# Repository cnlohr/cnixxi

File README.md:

# cnixxi

My experiment with nixie tubes.

It uses a ch32v003 to both control the nixie tube's cathodes, as well as provide the 180V supply for the nixie tube.

Youtube video:

Schematic:

Board:

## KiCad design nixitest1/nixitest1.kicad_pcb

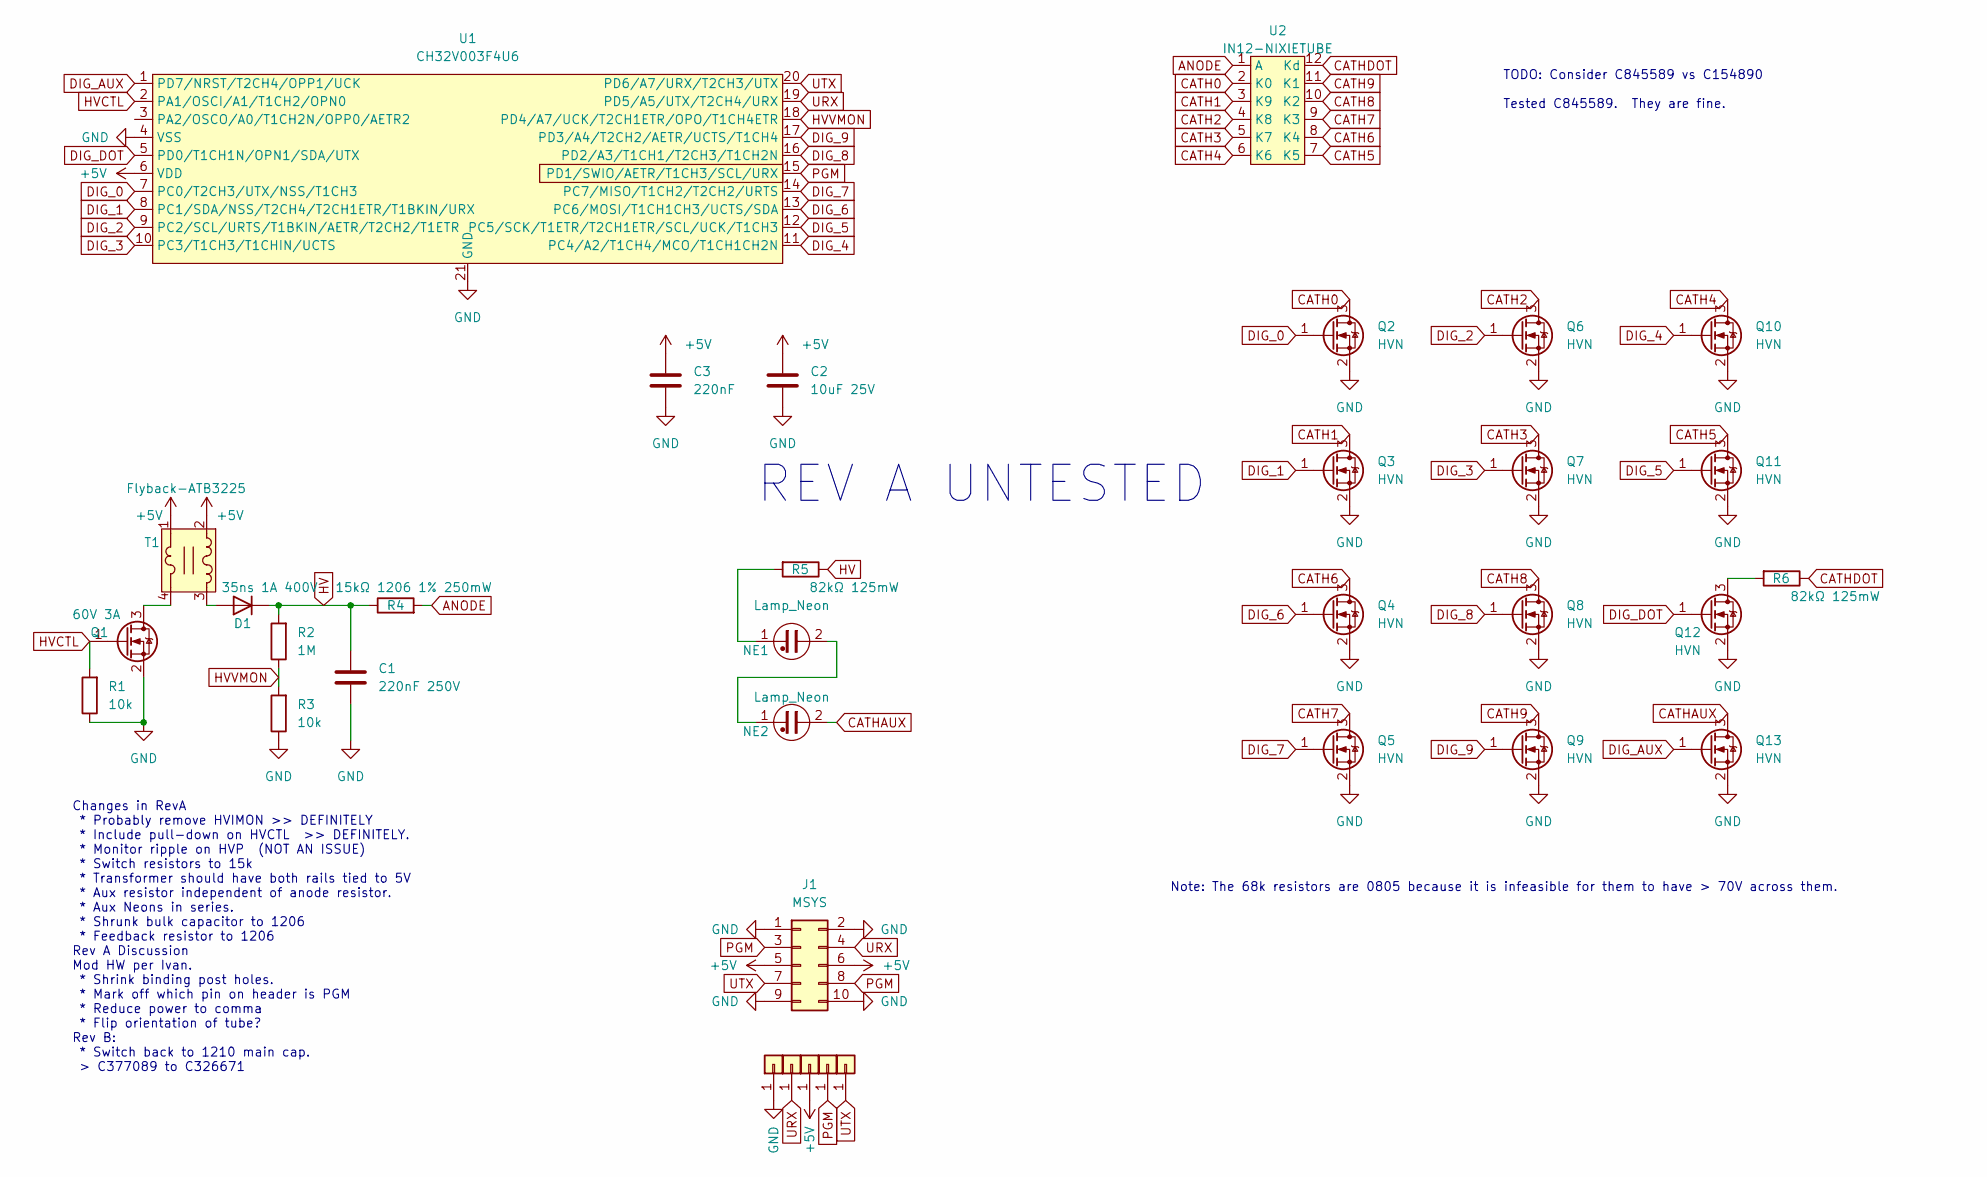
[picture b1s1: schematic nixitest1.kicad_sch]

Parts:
C1: 220nF 250V; C_1210_3225Metric; LCSC C326671
C2: 10uF 25V; C_0603_1608Metric; LCSC C96446
C3: 220nF; C_0402_1005Metric; LCSC C16772
D1: 35ns 1A 400V; D_SOD-123F; LCSC C128697
J1: MSYS; PinHeader_2x05_P2.54mm_Horizontal; LCSC C239336
J2, J3, J4, J5, J6: rawpad22
NE1, NE2: Lamp_Neon; neonglow
Q1: 60V 3A; SOT-23; LCSC C2938374
Q2, Q3, Q4, Q5, Q6, Q7, Q8, Q9, Q10, Q11, Q12, Q13: HVN; SOT-23; LCSC C845589
R1, R3: 10k; R_0402_1005Metric; LCSC C25744
R2: 1M; R_1206_3216Metric; LCSC C108083
R4: 15kΩ 1206 1% 250mW; R_1206_3216Metric; LCSC C114932
R5, R6: 82kΩ 125mW; R_0805_2012Metric; LCSC C136904
T1: Flyback-ATB3225; LCSC C415291
U1: CH32V003F4U6; QFN-20-1EP_3x3mm_P0.4mm_EP1.65x1.65mm; LCSC C5299908
U2: IN12-NIXIETUBE; IN12-NIXIE

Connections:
+5V: C2.1, C3.1, J1.5, J1.6, J3.1, T1.1, T1.2, U1.6 (VDD)
ANODE: R4.2, U2.1 (A)
CATH0: Q2.3 (D), U2.2 (K0)
CATH1: Q3.3 (D), U2.3 (K9)
CATH2: Q6.3 (D), U2.4 (K8)
CATH3: Q7.3 (D), U2.5 (K7)
CATH4: Q10.3 (D), U2.6 (K6)
CATH5: Q11.3 (D), U2.7 (K5)
CATH6: Q4.3 (D), U2.8 (K4)
CATH7: Q5.3 (D), U2.9 (K3)
CATH8: Q8.3 (D), U2.10 (K2)
CATH9: Q9.3 (D), U2.11 (K1)
CATHAUX: NE2.2, Q13.3 (D)
CATHDOT: R6.1, U2.12 (Kd)
DIG_0: Q2.1 (G), U1.7 (PC0/T2CH3/UTX/NSS/T1CH3)
DIG_1: Q3.1 (G), U1.8 (PC1/SDA/NSS/T2CH4/T2CH1ETR/T1BKIN/URX)
DIG_2: Q6.1 (G), U1.9 (PC2/SCL/URTS/T1BKIN/AETR/T2CH2/T1ETR)
DIG_3: Q7.1 (G), U1.10 (PC3/T1CH3/T1CHIN/UCTS)
DIG_4: Q10.1 (G), U1.11 (PC4/A2/T1CH4/MCO/T1CH1CH2N)
DIG_5: Q11.1 (G), U1.12 (PC5/SCK/T1ETR/T2CH1ETR/SCL/UCK/T1CH3)
DIG_6: Q4.1 (G), U1.13 (PC6/MOSI/T1CH1CH3/UCTS/SDA)
DIG_7: Q5.1 (G), U1.14 (PC7/MISO/T1CH2/T2CH2/URTS)
DIG_8: Q8.1 (G), U1.16 (PD2/A3/T1CH1/T2CH3/T1CH2N)
DIG_9: Q9.1 (G), U1.17 (PD3/A4/T2CH2/AETR/UCTS/T1CH4)
DIG_AUX: Q13.1 (G), U1.1 (PD7/NRST/T2CH4/OPP1/UCK)
DIG_DOT: Q12.1 (G), U1.5 (PD0/T1CH1N/OPN1/SDA/UTX)
GND: C1.2, C2.2, C3.2, J1.1, J1.2, J1.9, J1.10, J2.1, Q1.2 (S), Q2.2 (S), Q3.2 (S), Q4.2 (S), Q5.2 (S), Q6.2 (S), Q7.2 (S), Q8.2 (S), Q9.2 (S), Q10.2 (S), Q11.2 (S), Q12.2 (S), Q13.2 (S), R1.1, R3.1, U1.4 (VSS), U1.21 (GND)
HV: C1.1, D1.1 (K), R2.2, R4.1, R5.1
HVCTL: Q1.1 (G), R1.2, U1.2 (PA1/OSCI/A1/T1CH2/OPN0)
HVVMON: R2.1, R3.2, U1.18 (PD4/A7/UCK/T2CH1ETR/OPO/T1CH4ETR)
unnamed: D1.2 (A), T1.3
unnamed: NE1.1, R5.2
unnamed: NE1.2, NE2.1
unnamed: Q1.3 (D), T1.4
unnamed: Q12.3 (D), R6.2
PGM: J1.3, J1.8, J5.1, U1.15 (PD1/SWIO/AETR/T1CH3/SCL/URX)
URX: J1.4, J4.1, U1.19 (PD5/A5/UTX/T2CH4/URX)
UTX: J1.7, J6.1, U1.20 (PD6/A7/URX/T2CH3/UTX)

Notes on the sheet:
TODO: Consider C845589 vs C154890 Tested C845589. They are fine.
Changes in RevA * Probably remove HVIMON >> DEFINITELY * Include pull-down on HVCTL >> DEFINITELY. * Monitor ripple on HVP (NOT AN ISSUE) * Switch resistors to 15k * Transformer should have both rails tied to 5V * Aux resistor independent of anode resistor. * Aux Neons in series. * Shrunk bulk capa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
REV A UNTESTED
Note: The 68k resistors are 0805 because it is infeasible for them to have > 70V across them.

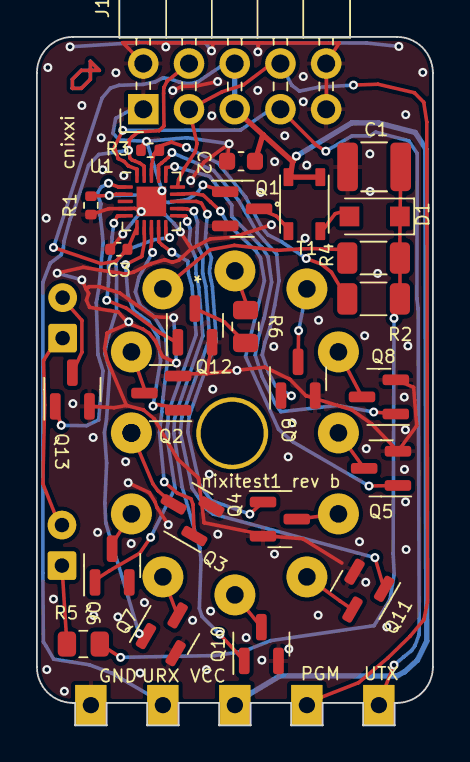
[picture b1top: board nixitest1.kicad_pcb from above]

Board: 2 copper layers, 22.0 x 38.2 mm, 34 parts (0 on the bottom side), 38 nets.

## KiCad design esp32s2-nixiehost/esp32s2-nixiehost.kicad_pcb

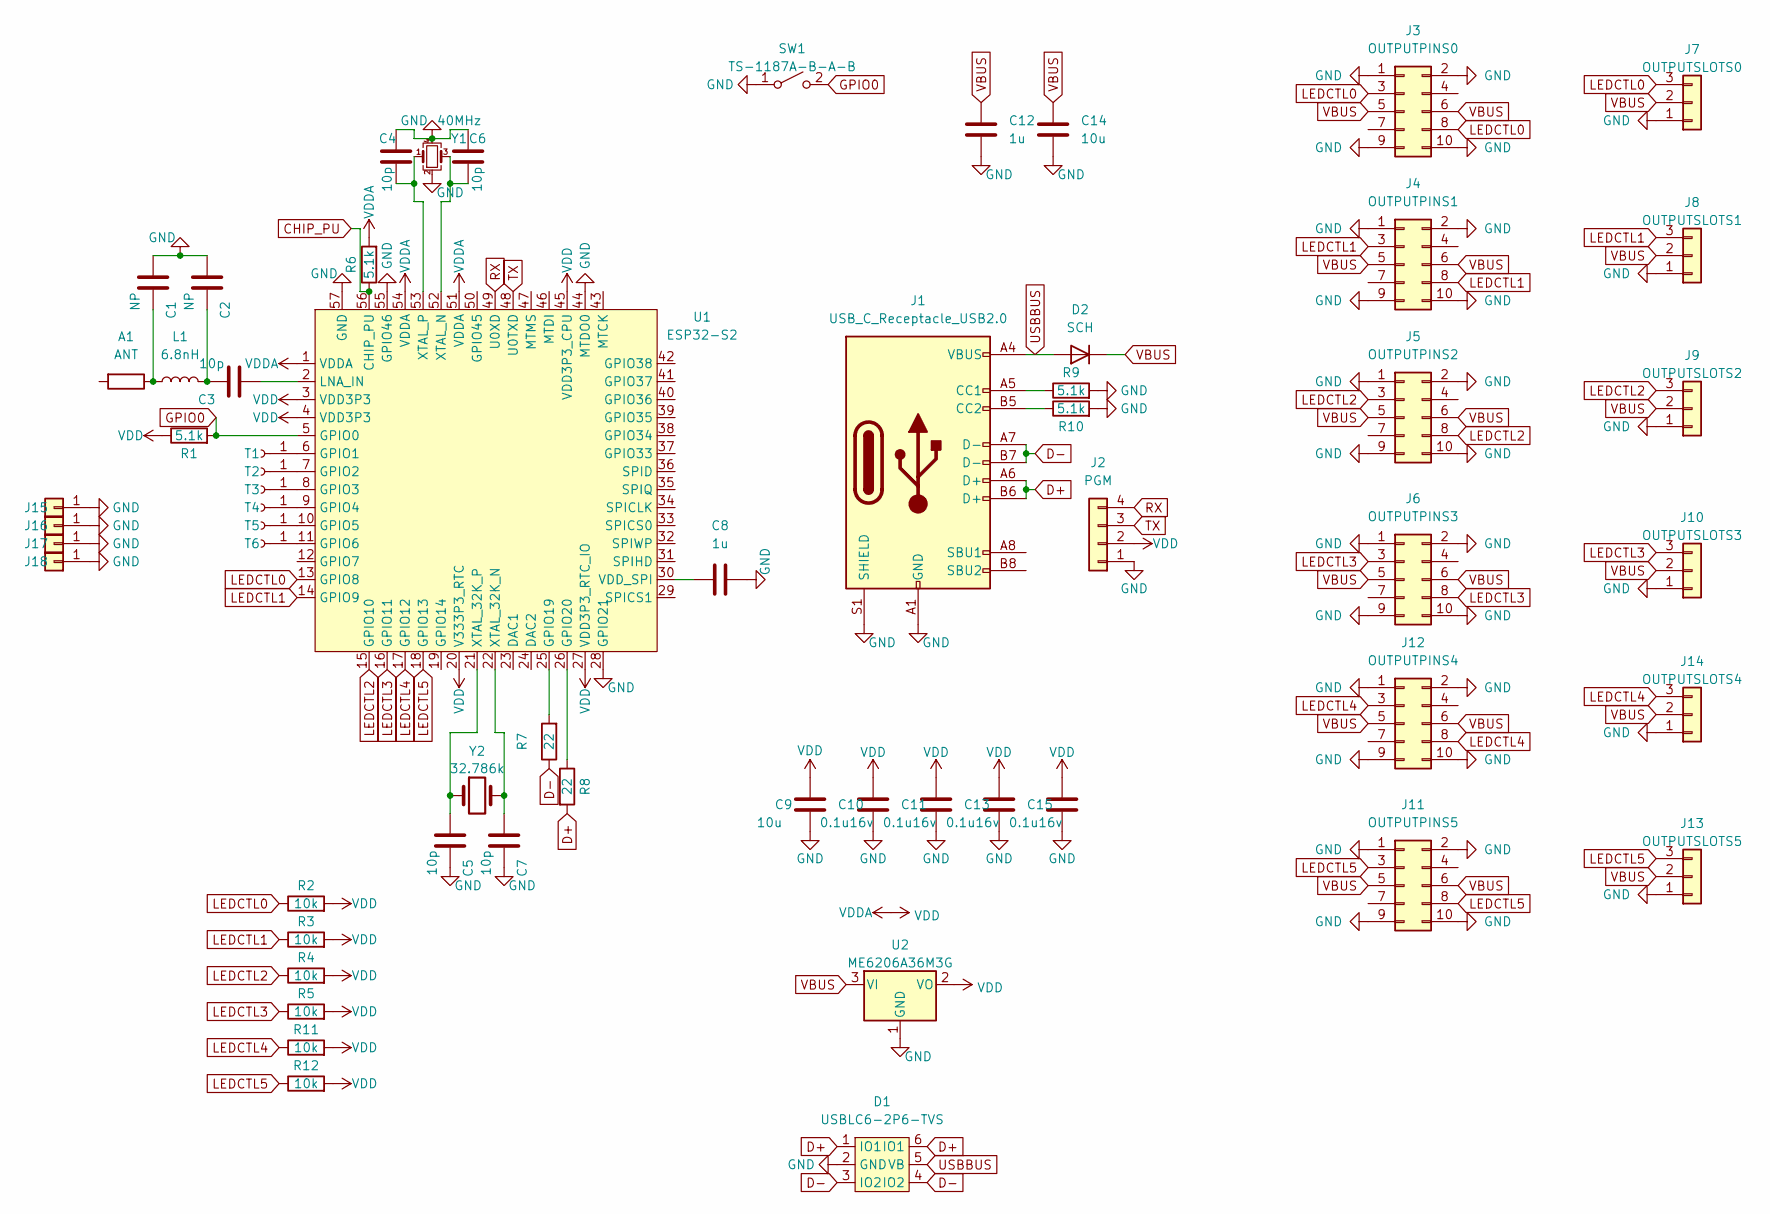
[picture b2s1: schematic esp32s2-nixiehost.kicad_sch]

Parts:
A1: ANT; R_1206_3216Metric; LCSC C127629
C1, C2: NP; C_0402_1005Metric; LCSC C106199
C3, C4, C5, C6, C7: 10p; C_0402_1005Metric; LCSC C106199
C8, C12: 1u; C_0402_1005Metric; LCSC C106254
C9: 10u; C_0402_1005Metric; LCSC C315248
C10, C11, C13, C15: 0.1u16v; C_0402_1005Metric; LCSC C338032
C14: 10u; C_0603_1608Metric; LCSC C18800
D1: USBLC6-2P6-TVS; SOT-666; LCSC C2827693
D2: SCH; D_SOD-123F; LCSC C115330
J1: USB_C_Receptacle_USB2.0; USB_C_Receptacle_HRO_TYPE-C-31-M-12; LCSC C2765186
J2: PGM; PinHeader_1x04_P2.54mm_Vertical; LCSC NP
J3: OUTPUTPINS0; PinSocket_2x05_P2.54mm_Vertical_SMD; LCSC C843271
J4: OUTPUTPINS1; PinSocket_2x05_P2.54mm_Vertical_SMD; LCSC C843271
J5: OUTPUTPINS2; PinSocket_2x05_P2.54mm_Vertical_SMD; LCSC C843271
J6: OUTPUTPINS3; PinSocket_2x05_P2.54mm_Vertical_SMD; LCSC C843271
J7: OUTPUTSLOTS0; nixiehostslot
J8: OUTPUTSLOTS1; nixiehostslot
J9: OUTPUTSLOTS2; nixiehostslot
J10: OUTPUTSLOTS3; nixiehostslot
J11: OUTPUTPINS5; PinSocket_2x05_P2.54mm_Vertical_SMD; LCSC C843271
J12: OUTPUTPINS4; PinSocket_2x05_P2.54mm_Vertical_SMD; LCSC C843271
J13: OUTPUTSLOTS5; nixiehostslot
J14: OUTPUTSLOTS4; nixiehostslot
J15, J16, J17, J18: MountingHole_3.5mm_Pad
L1: 6.8nH; L_0402_1005Metric; LCSC C77110
R1, R6, R9, R10: 5.1k; R_0402_1005Metric; LCSC C105872
R2, R3, R4, R5, R11, R12: 10k; R_0402_1005Metric; LCSC C25086
R7, R8: 22; R_0402_1005Metric; LCSC C25092
SW1: TS-1187A-B-A-B; SW_SPST_TL3342; LCSC C318884
T1, T2, T3, T4, T5, T6: TOUCH; TouchExposed6
U1: ESP32-S2; ESP32S2; LCSC C2840995
U2: ME6206A36M3G; SOT-23; LCSC C236698
Y1: 40MHz; Crystal_SMD_2016-4Pin_2.0x1.6mm; LCSC C648970
Y2: 32.786k; Crystal_SMD_2012-2Pin_2.0x1.2mm; LCSC C99009

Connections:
CHIP_PU: R6.1, U1.56 (CHIP_PU)
D+: D1.1 (IO1), D1.6 (IO1), J1.A6 (D+), J1.B6 (D+), R8.2
D-: D1.3 (IO2), D1.4 (IO2), J1.A7 (D-), J1.B7 (D-), R7.1
GND: C1.2, C2.2, C4.1, C5.1, C6.1, C7.1, C8.2, C9.2, C10.2, C11.2, C12.1, C13.2, C14.2, C15.2, D1.2 (GND), J1.A1 (GND), J1.A12 (GND), J1.B1 (GND), J1.B12 (GND), J1.S1 (SHIELD), J2.1, J3.1, J3.2, J3.9, J3.10, J4.1, J4.2, J4.9, J4.10, J5.1, J5.2, J5.9, J5.10, J6.1, J6.2, J6.9, J6.10, J7.1, J8.1, J9.1, J10.1, J11.1, J11.2, J11.9, J11.10, J12.1, J12.2, J12.9, J12.10, J13.1, J14.1, J15.1, J16.1, J17.1, J18.1, R9.2, R10.2, SW1.1 (A), U1.28 (GPIO21), U1.44 (MTDO0), U1.55 (GPIO46), U1.57 (GND), U2.1 (GND), Y1.2, Y1.4
GPIO0: R1.2, SW1.2 (B), U1.5 (GPIO0)
LEDCTL0: J3.3, J3.8, J7.3, R2.1, U1.13 (GPIO8)
LEDCTL1: J4.3, J4.8, J8.3, R3.1, U1.14 (GPIO9)
LEDCTL2: J5.3, J5.8, J9.3, R4.1, U1.15 (GPIO10)
LEDCTL3: J6.3, J6.8, J10.3, R5.1, U1.16 (GPIO11)
LEDCTL4: J12.3, J12.8, J14.3, R11.1, U1.17 (GPIO12)
LEDCTL5: J11.3, J11.8, J13.3, R12.1, U1.18 (GPIO13)
unnamed: A1.1, C1.1, L1.1
unnamed: C2.1, C3.1, L1.2
unnamed: C3.2, U1.2 (LNA_IN)
unnamed: C4.2, U1.53 (XTAL_P), Y1.1
unnamed: C5.2, U1.21 (XTAL_32K_P), Y2.1
unnamed: C6.2, U1.52 (XTAL_N), Y1.3
unnamed: C7.2, U1.22 (XTAL_32K_N), Y2.2
unnamed: C8.1, U1.30 (VDD_SPI)
unnamed: J1.A5 (CC1), R9.1
unnamed: J1.B5 (CC2), R10.1
unnamed: R7.2, U1.25 (GPIO19)
unnamed: R8.1, U1.26 (GPIO20)
unnamed: T1.1, U1.6 (GPIO1)
unnamed: T2.1, U1.7 (GPIO2)
unnamed: T3.1, U1.8 (GPIO3)
unnamed: T4.1, U1.9 (GPIO4)
unnamed: T5.1, U1.10 (GPIO5)
unnamed: T6.1, U1.11 (GPIO6)
RX: J2.4, U1.49 (U0XD)
TX: J2.3, U1.48 (U0TXD)
USBBUS: D1.5 (VB), D2.2 (A), J1.A4 (VBUS), J1.A9 (VBUS), J1.B4 (VBUS), J1.B9 (VBUS)
VBUS: C12.2, C14.1, D2.1 (K), J3.5, J3.6, J4.5, J4.6, J5.5, J5.6, J6.5, J6.6, J7.2, J8.2, J9.2, J10.2, J11.5, J11.6, J12.5, J12.6, J13.2, J14.2, U2.3 (VI)
VDD: C9.1, C10.1, C11.1, C13.1, C15.1, J2.2, R1.1, R2.2, R3.2, R4.2, R5.2, R6.2, R11.2, R12.2, U1.1 (VDDA), U1.3 (VDD3P3), U1.4 (VDD3P3), U1.20 (V333P3_RTC), U1.27 (VDD3P3_RTC_IO), U1.45 (VDD3P3_CPU), U1.51 (VDDA), U1.54 (VDDA), U2.2 (VO)

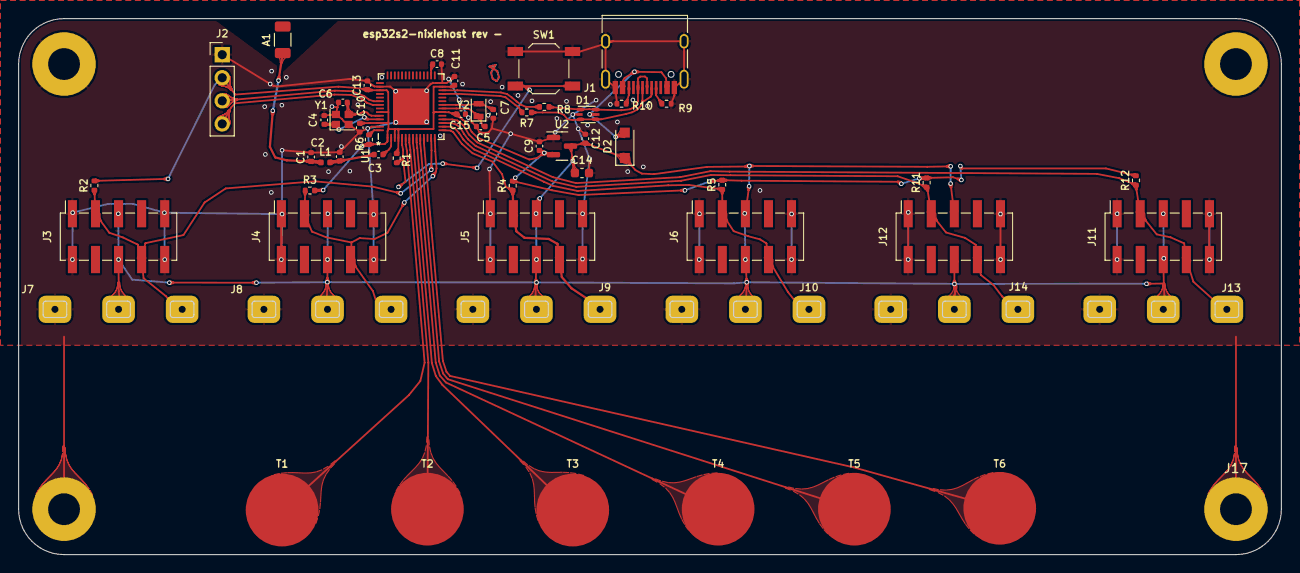
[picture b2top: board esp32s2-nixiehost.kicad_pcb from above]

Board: 2 copper layers, 139.0 x 59.0 mm, 60 parts (0 on the bottom side), 34 nets.

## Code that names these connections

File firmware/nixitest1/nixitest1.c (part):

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	RCC->APB1PRSTR |= RCC_APB1Periph_TIM2;
	RCC->APB1PRSTR &= ~RCC_APB1Periph_TIM2;

	// PD7 will be used as Timer 2, Channel 4 Configure timer 2 to enable this.
	//TIM2->SWEVGR = 0x0001; 			//TIM_PSCReloadMode_Immediate;

	TIM2->PSC = 0x0020;
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static void SetupADC()
{
	// Configure ADC.
	// PD4 is analog input chl 7
	GPIOD->CFGLR &= ~(0xf<<(4*4));	// CNF = 00: Analog, MODE = 00: Input
	
	// Reset the ADC to init all regs
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
	GPIOD->CFGLR = 
		(GPIO_Speed_10MHz | GPIO_CNF_OUT_PP)<<(4*6) | // GPIO D6 Debug
		(GPIO_Speed_10MHz | GPIO_CNF_OUT_PP_AF)<<(4*7) | // DIG_AUX  (TIM2CH4)
		(GPIO_Speed_10MHz | GPIO_CNF_OUT_PP)<<(4*3) | // DIG_9
		(GPIO_Speed_10MHz | GPIO_CNF_OUT_PP)<<(4*2) | // DIG_8
		(GPIO_Speed_10MHz | GPIO_CNF_IN_FLOATING)<<(4*1) | // PGM Floats.
		(GPIO_Speed_10MHz | GPIO_CNF_OUT_PP)<<(4*0);  // DIG_DOT

	GPIOC->CFGLR = 
		(GPIO_Speed_10MHz | GPIO_CNF_OUT_PP)<<(4*0) | // DIG_0
		(GPIO_Speed_10MHz | GPIO_CNF_OUT_PP)<<(4*1) | // DIG_1
		(GPIO_Speed_10MHz | GPIO_CNF_OUT_PP)<<(4*2) | // DIG_2
		(GPIO_Speed_10MHz | GPIO_CNF_OUT_PP)<<(4*3) | // DIG_3
		(GPIO_Speed_10MHz | GPIO_CNF_OUT_PP)<<(4*4) | // DIG_4
		(GPIO_Speed_10MHz | GPIO_CNF_OUT_PP)<<(4*5) | // DIG_5
		(GPIO_Speed_10MHz | GPIO_CNF_OUT_PP)<<(4*6) | // DIG_6
		(GPIO_Speed_10MHz | GPIO_CNF_OUT_PP)<<(4*7);  // DIG_7


	GPIOA->CFGLR =
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
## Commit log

2023-01-23 Add initial commit, thoughts.
2023-04-13 Add test board
2023-04-13 Add flyback.
2023-04-14 Update design.
2023-04-14 Ok actually ready for production.
2023-04-18 Update parts.
2023-04-19 Add start of nixiehost
2023-04-20 Bump to rel ver
2023-04-21 Update comments on nixietest + Add debug tool. + Add ch32v003 firmware for the controller.
2023-04-21 Update board design
2023-04-21 General update for all
2023-04-22 Update projects with notes. Allow for tuning.
2023-04-22 100% working! Variable input voltage.
2023-04-22 WOOT! I think this is "done"
2023-04-23 * Revert pcb so it matches production files. * Move original thoughts into attic. * Update comments on firmware
2023-04-23 Update code
2023-04-23 Update submodule
2023-04-23 Update with a lot of comments.
2023-04-23 Fully documented and tuned loop.
2023-04-23 Oops forgot one note.
2023-04-23 Ok really one lastmessage.
2023-04-23 Update slider so it is over the right range.
2023-04-23 Try switching to a 12MHz ADC clock as per recommendations in datasheet.
2023-04-23 Much better tuning - before trying to do something different.
2023-04-23 Good tuning parameters across whole voltage range.
2023-04-24 Update tuning for off time and general testing.
2023-04-24 Update with watchdog discussion.
2023-04-24 Update with more comments.
2023-04-24 Cleanup a little.
2023-04-24 Update! Add good optionbytes
2023-04-24 Update with Aux neon control
2023-04-24 Don't allow negative neonglow.
2023-04-24 Update design based on tests of first rev.
2023-04-24 Forgot to mention testing orientation differences?
2023-04-25 Improve perf of adc interrupt + retune
2023-04-25 Add fast multiply. And improve tuning for updated situation. Also super increase chopping frequency.
2023-04-25 retuned to prevent hissing.
2023-04-25 Update schematic and design.
2023-04-25 Add note about assembly.
2023-04-27 Adjust resistors to reduce max power to neons and period.
2023-04-30 Updte with schematic.
2023-04-30 Tweak pins.
2023-04-30 Update footprints to shrink holes for standoffs.
2023-05-06 Update testing app + bump ch32v003fun
2023-05-06 Fix Makefile for building test apps.
2023-05-06 Properly set up interface for using as DLL.
2023-05-06 Bump submodule
2023-05-06 Update, switching to srodata.
2023-05-06 Update for use with link-E
2023-05-06 Add windows buttons.
2023-05-07 Update ch32v003fun repo
2023-06-08 Update to rev B.
2023-06-09 Update schematic etc for rev b.
2023-06-09 Update firmware
2023-06-09 Update holes for tubes.
2024-04-25 Remove incorrect comment
2024-04-25 Fix incorrect timer 2 setup note.
2024-04-25 Oops incorrect - remove note
2025-08-04 Update with schematic etc.

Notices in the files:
firmware/nixitest1/nixitest1.c:
Copyright 2023 <>< Charles Lohr, under the MIT-X11 license or NewBSD
